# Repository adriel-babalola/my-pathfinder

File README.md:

# My-pathfinder

## What is it?

its a modified version of the pathfinder starter project. i added an extra LED, an extra switch, and a buzzer. so now whenever you press a button it makes a sound.

## Why i made it

i originally wanted to make a pomodoro timer but honestly it was way too complex for where i was. i kept getting stuck on diagrams i didn't understand and i wasn't making any progress. so i thought, instead of going that deep, why not just take what i know and add something to it. i knew how the switches and LEDs worked from pathfinder already, and making a buzzer sound is literally just a digitalWrite so i added that. its my first time doing hardware so i kept it simple on purpose.

---

## Pictures

**3D Model**

**PCB**

---

## BOM
 
| Designator | Part | Quantity | Unit Price (USD) | Total (USD) | Supplier | Link |
|---|---|---|---|---|---|---|
| BZ1 | Passive Buzzer 9042 16ohm AC 3V/3.3V | 1 | $1.04 | $1.04 | AliExpress | [Link](https://www.aliexpress.com/item/1005008414603547.html) |
| U1 | RP2040-Zero (Raspberry Pi Pico-compatible) | 1 | $1.51 | $1.51 | AliExpress | [Link](https://www.aliexpress.com/item/1005003796360532.html) |
| SW1–SW4 | Gateron KS-9 Mechanical Switch (White) | 4 | — | $3.92 | AliExpress | [Link](https://www.aliexpress.com/item/1005007380739304.html) |
| D1–D4 | 10mm Round Top Super Bright White LED | 4 | — | $3.55 | AliExpress | [Link](https://www.aliexpress.com/item/1005007931873474.html) |
| R1–R4 | 220R Carbon Film Resistor 1/2W 5% | 4 | — | $1.04 | AliExpress | [Link](https://www.aliexpress.com/item/1005007551484723.html) |
| R5 | 100R Carbon Film Resistor 1/2W 5% | 1 | — | $0.97 | AliExpress | [Link](https://www.aliexpress.com/item/1005007551484723.html) |
| — | Custom PCB (JLCPCB) | 5 | — | $2.00 | JLCPCB | — |
 
**Total: $14.03**

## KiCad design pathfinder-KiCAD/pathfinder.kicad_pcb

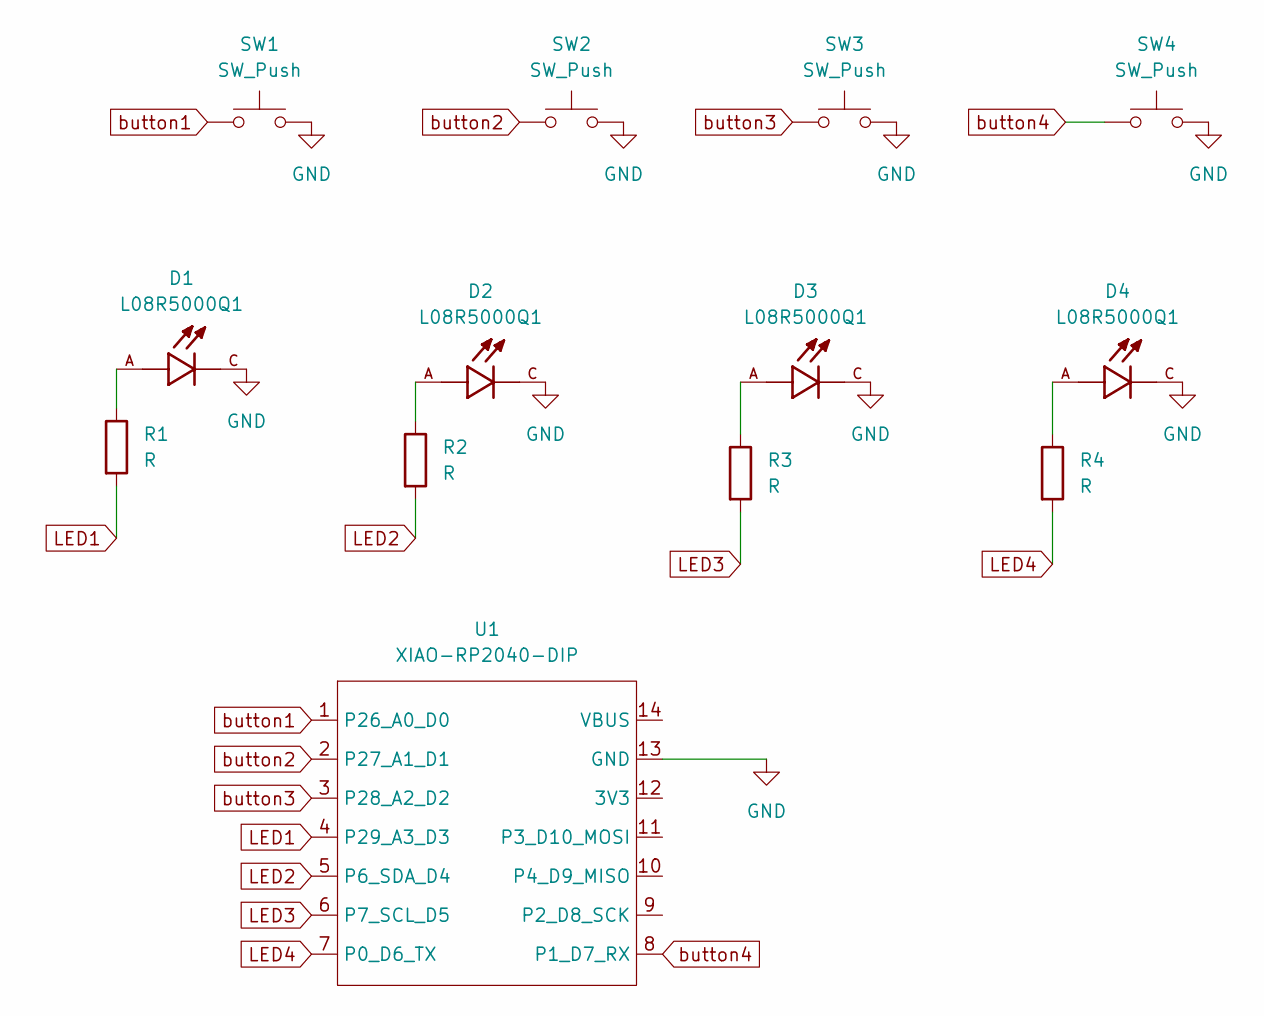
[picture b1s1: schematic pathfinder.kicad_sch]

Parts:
D1, D2, D3, D4: L08R5000Q1; LEDRD254W57D500H1070; PARTREV NA
R1, R2, R3, R4: R; R_Axial_DIN0204_L3.6mm_D1.6mm_P5.08mm_Horizontal
SW1, SW2, SW3, SW4: SW_Push; SW_Cherry_MX_1.00u_PCB
U1: XIAO-RP2040-DIP

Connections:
GND: D1.C, D2.C, D3.C, D4.C, SW1.2, SW2.2, SW3.2, SW4.2, U1.13 (GND)
LED1: R1.2, U1.4 (P29_A3_D3)
LED2: R2.2, U1.5 (P6_SDA_D4)
LED3: R3.2, U1.6 (P7_SCL_D5)
LED4: R4.2, U1.7 (P0_D6_TX)
unnamed: D1.A, R1.1
unnamed: D2.A, R2.1
unnamed: D3.A, R3.1
unnamed: D4.A, R4.1
button1: SW1.1, U1.1 (P26_A0_D0)
button2: SW2.1, U1.2 (P27_A1_D1)
button3: SW3.1, U1.3 (P28_A2_D2)
button4: SW4.1, U1.8 (P1_D7_RX)

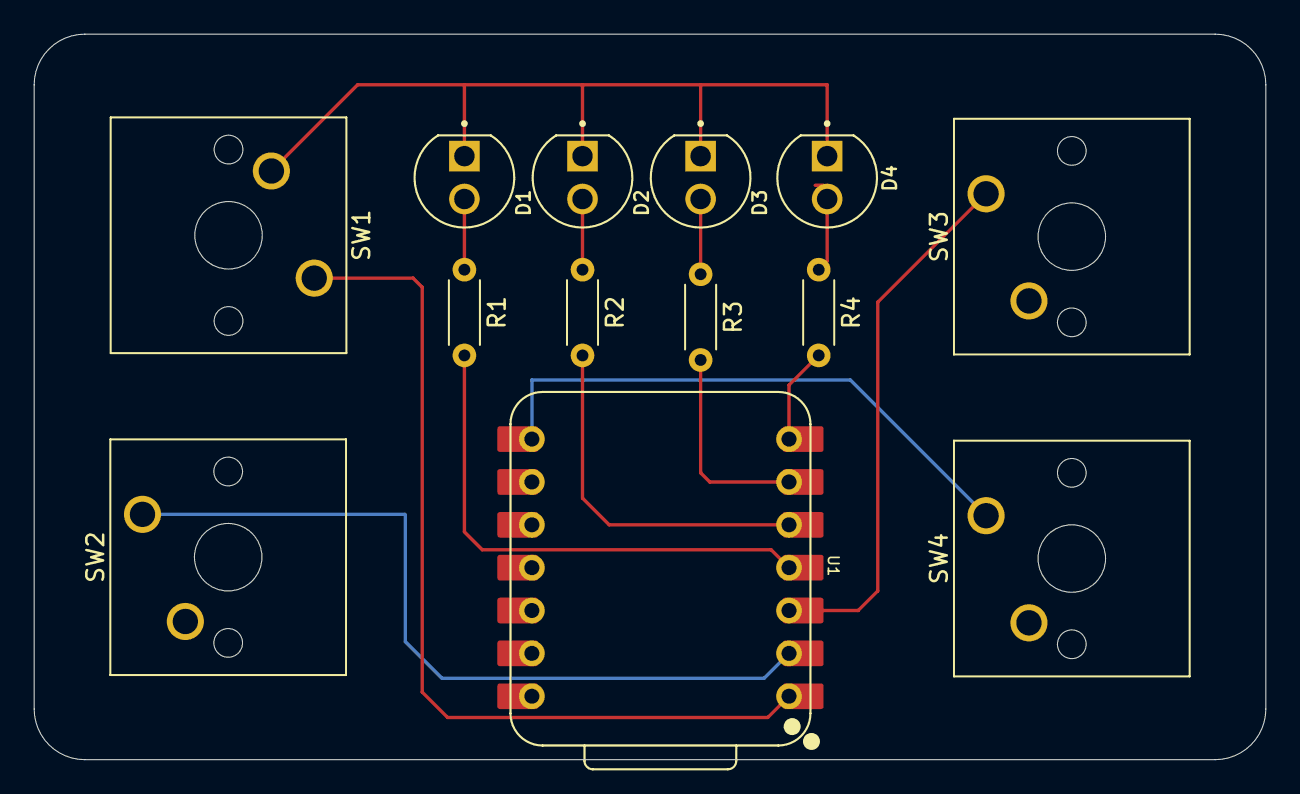
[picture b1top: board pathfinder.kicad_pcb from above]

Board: 2 copper layers, 73.0 x 43.0 mm, 13 parts (0 on the bottom side), 13 nets.

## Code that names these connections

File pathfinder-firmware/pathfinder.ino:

int BUT1 = D0;
int BUT2 = D1;
int BUT3 = D2;
int BUT4 = D7;

int LED1 = D3;
int LED2 = D4;
int LED3 = D5;
int LED4 = D6;

void setup() {
  pinMode(BUT1, INPUT_PULLUP);
  pinMode(BUT2, INPUT_PULLUP);
  pinMode(BUT3, INPUT_PULLUP);
  pinMode(BUT4, INPUT_PULLUP);


  pinMode(LED1, OUTPUT);
  pinMode(LED2, OUTPUT);
  pinMode(LED3, OUTPUT);
  pinMode(LED4, OUTPUT);

  long startTime = millis();
}

void loop() {
  long but1time;
  long but2time;
  long but3time;
  long but4time = 0;

  if (digitalRead(BUT1) == HIGH) {
    but1time = millis();
    digitalWrite(LED1, HIGH);
  } else {
    digitalWrite(LED1, LOW);
  }

  if (digitalRead(BUT2) == HIGH) {
    but2time = millis();
    digitalWrite(LED2, HIGH);
  } else {
    digitalWrite(LED2, LOW);
  }

  if (digitalRead(BUT3) == HIGH) {
    but3time = millis();
    digitalWrite(LED3, HIGH);
  } else {
    digitalWrite(LED3, LOW);
  }

  if (digitalRead(BUT4) == HIGH) {
    but4time = millis();
    digitalWrite(LED4, HIGH);
  } else {
    digitalWrite(LED4, LOW);
  }


  if (abs(but2time - but1time) <= 2000) {
    digitalWrite(LED2, HIGH);
  } else {
    digitalWrite(LED2, LOW);
  }

  if (digitalRead(BUT3) == HIGH) {
    but3time++;
  } else {
    but3time = 0 ;
  }

  if (but3time >= 800 ) {
    digitalWrite(LED3, HIGH);
  } else {
    digitalWrite(LED3, LOW);
  }
}

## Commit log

2026-04-10 just finished the starter porject
2026-04-10 polished folder structure
2026-04-11 forgot to include pcb in BOM
2026-04-11 Add images for 3D model and PCB layout
    Added images for the 3D model and PCB layout in README.
